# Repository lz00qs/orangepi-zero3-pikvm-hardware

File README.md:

# orangepi-zero3-pikvm-hardware

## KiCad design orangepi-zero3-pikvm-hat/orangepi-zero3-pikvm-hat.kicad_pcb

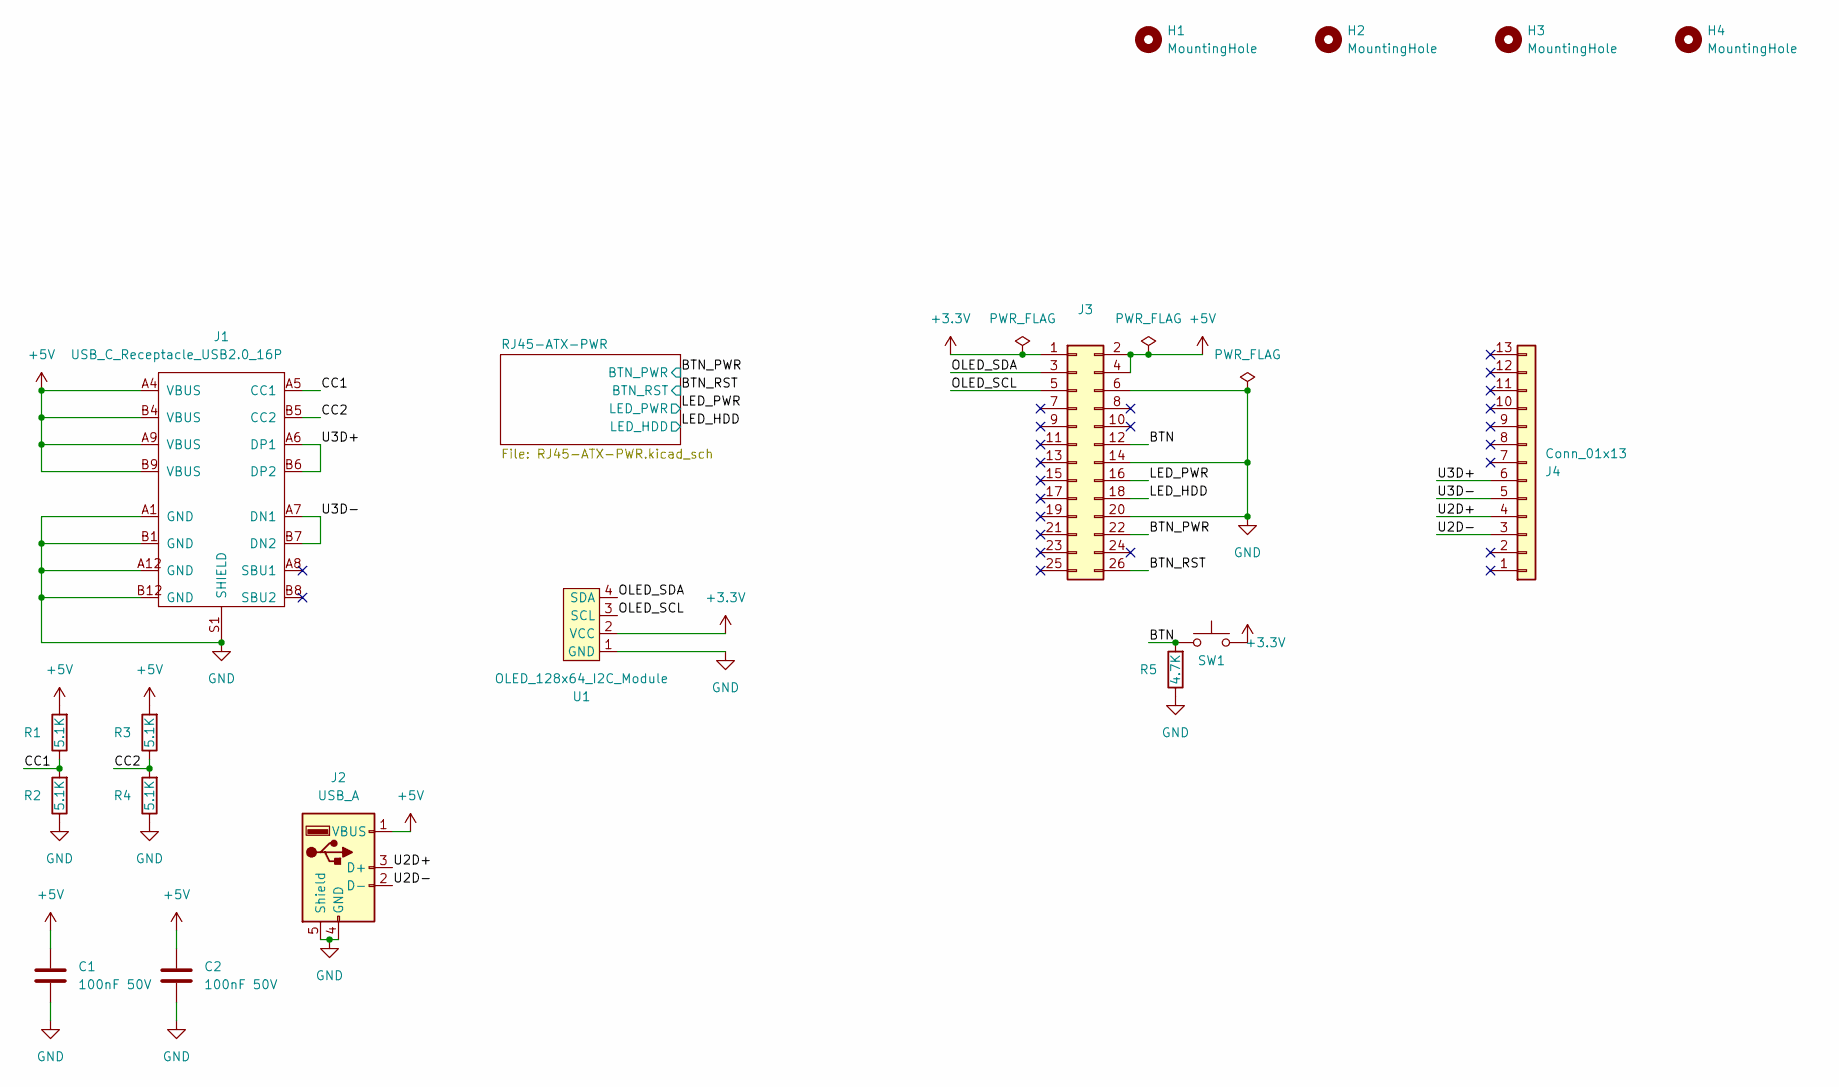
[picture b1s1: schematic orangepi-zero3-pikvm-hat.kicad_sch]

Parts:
C1, C2: 100nF 50V; C_0603_1608Metric
H1, H2, H3, H4: MountingHole; MountingHole_3mm
J1: USB_C_Receptacle_USB2.0_16P; USB_C_Receptacle_SMD_16P_USB2.0_JLC-31-M-12
J2: USB_A; USB_A_Wuerth_614004134726_Horizontal
J3: Conn_02x13_Odd_Even; PinHeader_2x13_P2.54mm_Vertical
J4: Conn_01x13; PinHeader_1x13_P2.54mm_Vertical
R1, R2, R3, R4: 5.1K; R_0402_1005Metric
R5: 4.7K; R_0603_1608Metric
SW1: SW_x1; SW-SMD_4P-L4.2-W3.3-P2.15-LS5.1
U1: OLED_128x64_I2C_Module; PinHeader_1x04_P2.54mm_Vertical

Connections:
+3.3V: J3.1, SW1.2, U1.2 (VCC); also elsewhere on the board
+5V: C1.1, C2.1, J1.A4 (VBUS), J1.A9 (VBUS), J1.B4 (VBUS), J1.B9 (VBUS), J2.1 (VBUS), J3.2, J3.4, R1.2, R3.2
/BTN: J3.12, R5.2, SW1.1
/BTN_PWR: J3.22; also elsewhere on the board
/BTN_RST: J3.26; also elsewhere on the board
/CC1: J1.A5 (CC1), R1.1, R2.2
/CC2: J1.B5 (CC2), R3.1, R4.2
/LED_HDD: J3.18; also elsewhere on the board
/LED_PWR: J3.16; also elsewhere on the board
/OLED_SCL: J3.5, U1.3 (SCL)
/OLED_SDA: J3.3, U1.4 (SDA)
/U2D+: J2.3 (D+), J4.4
/U2D-: J2.2 (D-), J4.3
/U3D+: J1.A6 (DP1), J1.B6 (DP2), J4.6
/U3D-: J1.A7 (DN1), J1.B7 (DN2), J4.5
GND: C1.2, C2.2, J1.A1 (GND), J1.A12 (GND), J1.B1 (GND), J1.B12 (GND), J1.S1 (SHIELD), J2.4 (GND), J2.5 (Shield), J3.6, J3.14, J3.20, R2.1, R4.1, R5.1, U1.1 (GND); also elsewhere on the board

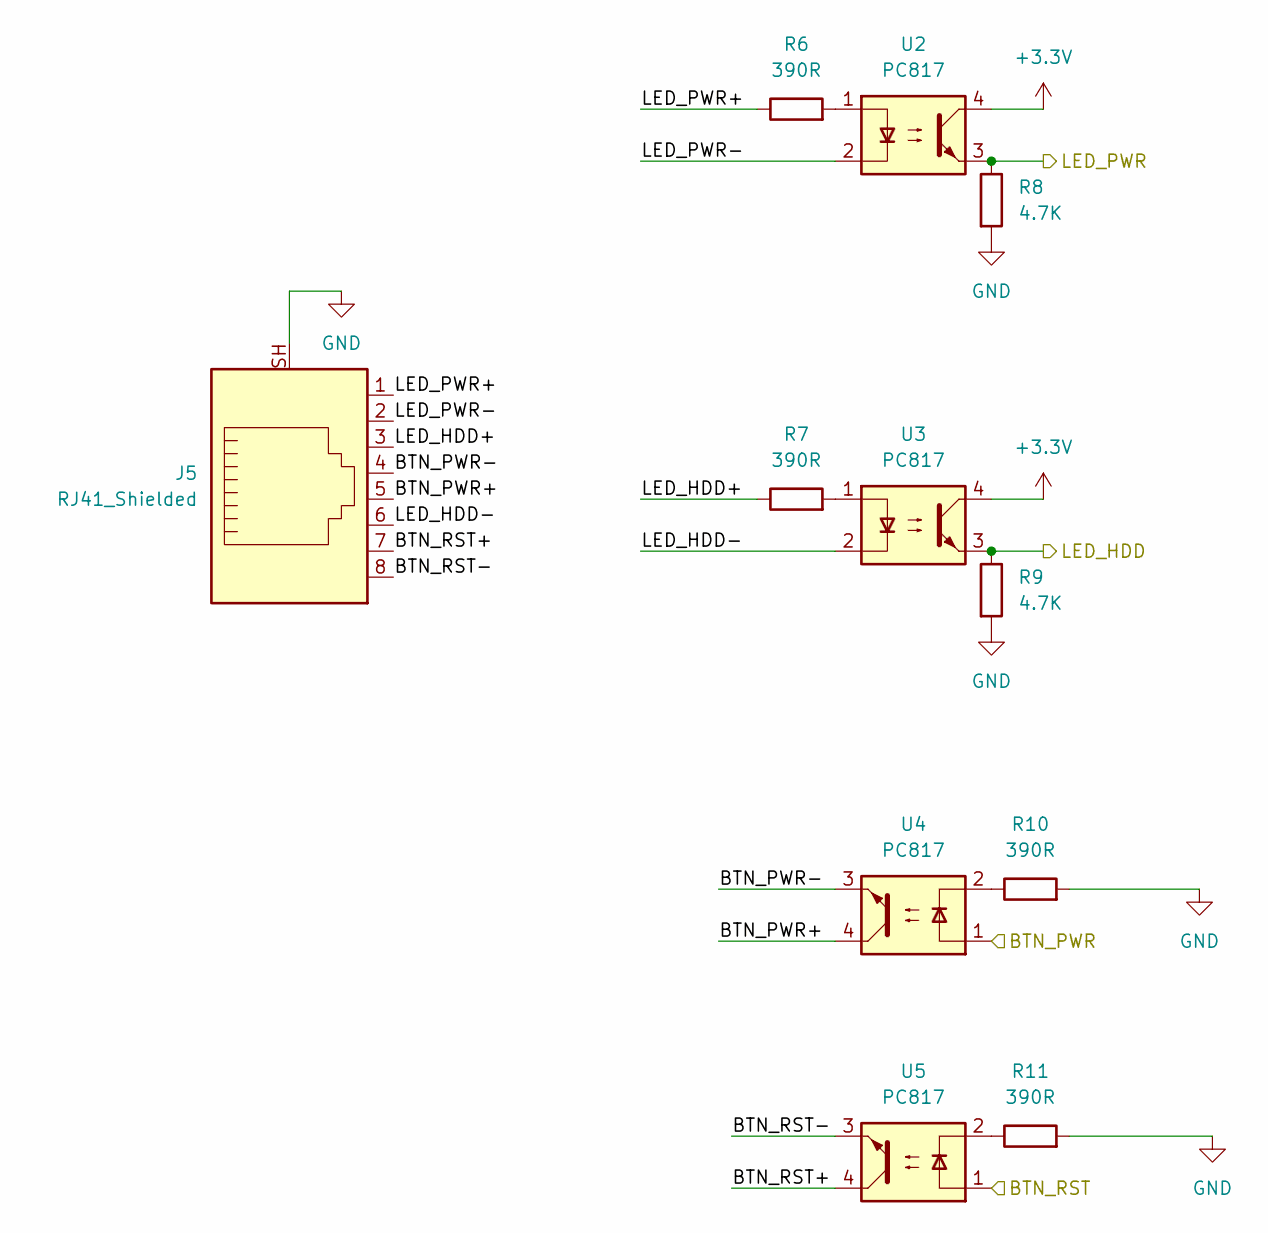
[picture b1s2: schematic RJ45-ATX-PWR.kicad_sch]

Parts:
J5: RJ41_Shielded; RJ45_Amphenol_RJHSE5380
R6, R7, R10, R11: 390R; R_0603_1608Metric
R8, R9: 4.7K; R_0603_1608Metric
U2, U3, U4, U5: PC817; SO-4_7.6x3.6mm_P2.54mm

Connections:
+3.3V: U2.4, U3.4; also elsewhere on the board
/BTN_PWR: U4.1; also elsewhere on the board
/BTN_RST: U5.1; also elsewhere on the board
/LED_HDD: R9.1, U3.3; also elsewhere on the board
/LED_PWR: R8.1, U2.3; also elsewhere on the board
/RJ45-ATX-PWR/BTN_PWR+: J5.5, U4.4
/RJ45-ATX-PWR/BTN_PWR-: J5.4, U4.3
/RJ45-ATX-PWR/BTN_RST+: J5.7, U5.4
/RJ45-ATX-PWR/BTN_RST-: J5.8, U5.3
/RJ45-ATX-PWR/LED_HDD+: J5.3, R7.1
/RJ45-ATX-PWR/LED_HDD-: J5.6, U3.2
/RJ45-ATX-PWR/LED_PWR+: J5.1, R6.1
/RJ45-ATX-PWR/LED_PWR-: J5.2, U2.2
GND: J5.SH, R8.2, R9.2, R10.2, R11.2; also elsewhere on the board
unnamed: R6.2, U2.1
unnamed: R7.2, U3.1
unnamed: R10.1, U4.2
unnamed: R11.1, U5.2

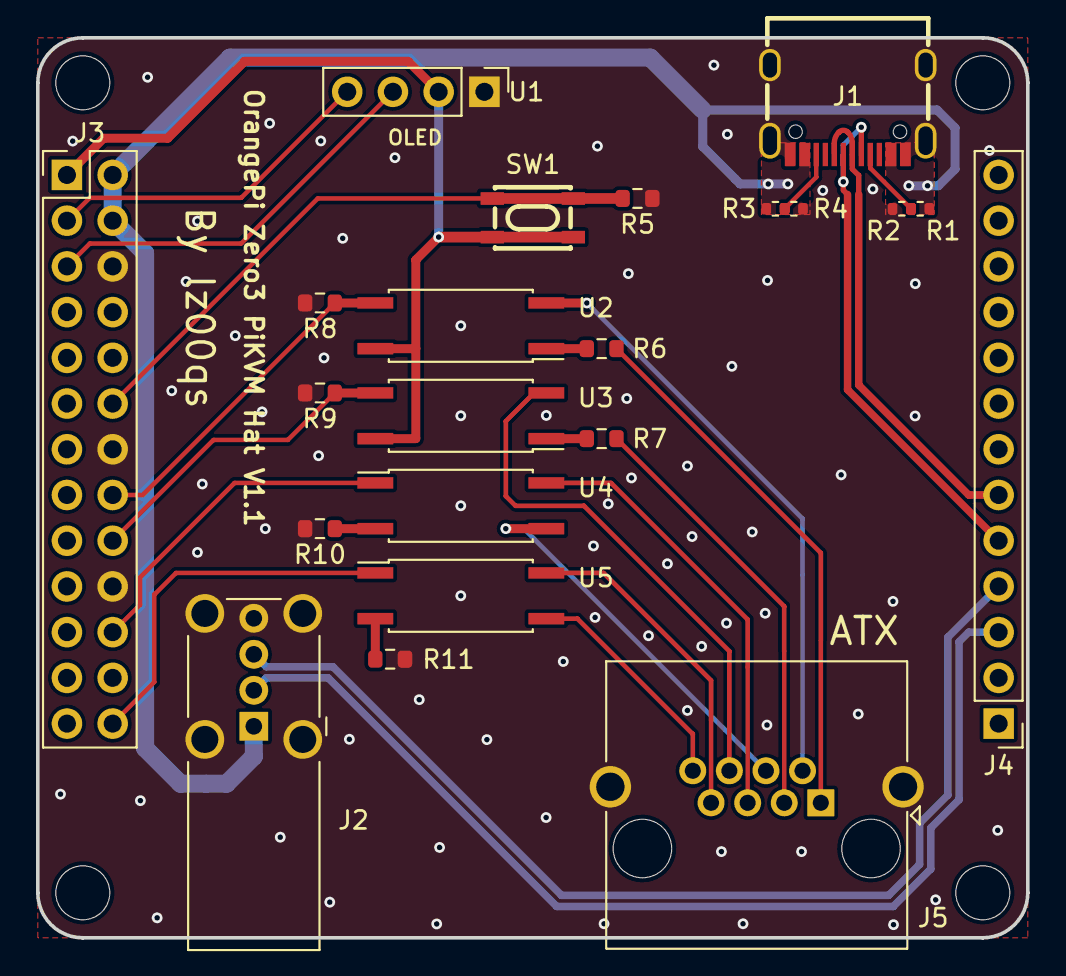
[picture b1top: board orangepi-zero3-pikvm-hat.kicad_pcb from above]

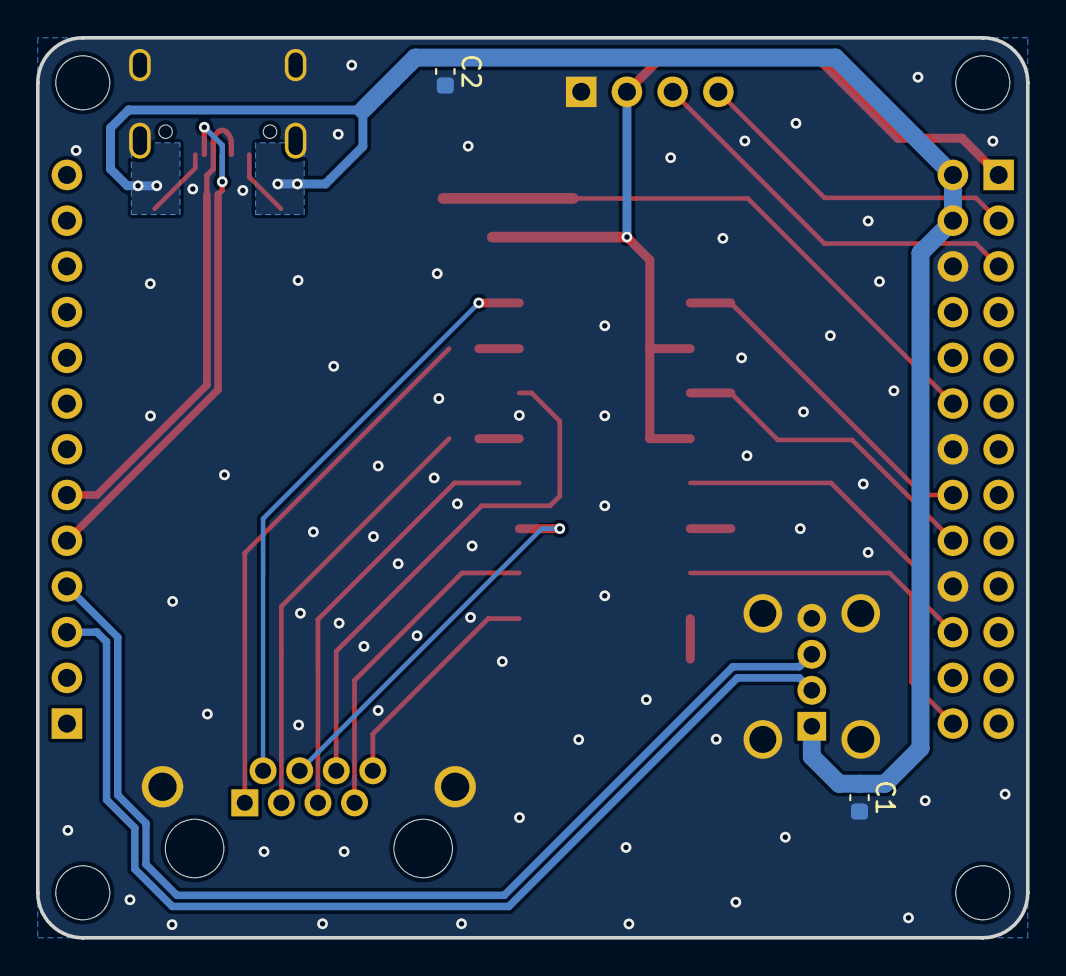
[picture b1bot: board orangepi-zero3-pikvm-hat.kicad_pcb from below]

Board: 2 copper layers, 55.0 x 50.0 mm, 28 parts (2 on the bottom side), 28 nets.

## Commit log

2023-12-10 Release V1.1 Hardware
2023-12-11 Optimised key size
